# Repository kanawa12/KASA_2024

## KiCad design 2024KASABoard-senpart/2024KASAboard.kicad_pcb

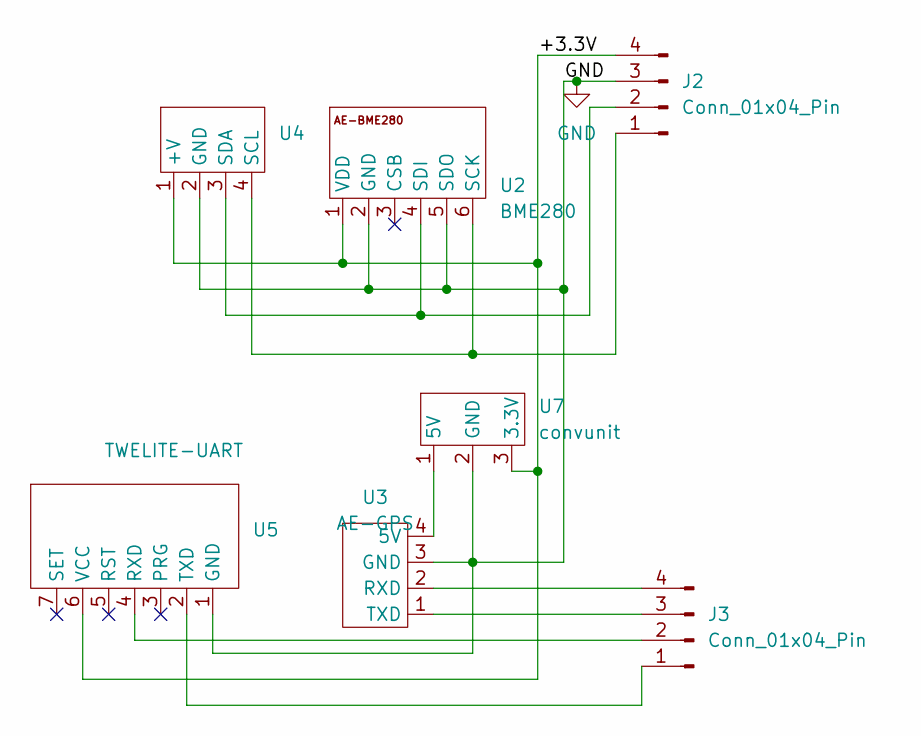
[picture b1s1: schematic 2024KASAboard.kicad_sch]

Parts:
J2, J3: Conn_01x04_Pin; JST_XH_S4B-XH-A_1x04_P2.50mm_Horizontal
U2: BME280; AE-BME280
U3: AE-GPS
U4: AE-LSM9DS1-I2C
U5: TWELITE-UART; MW-R-UART-U
U7: convunit; JST_VH_B3P-VH_1x03_P3.96mm_Vertical

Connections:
/+3.3V: J2.4, U2.1 (VDD), U4.1 (+V), U5.6 (VCC), U7.3 (3.3V)
GND: J2.3, U2.2 (GND), U2.5 (SDO), U3.3 (GND), U4.2 (GND), U5.1 (GND), U7.2 (GND)
unnamed: J2.1, U2.6 (SCK), U4.4 (SCL)
unnamed: J2.2, U2.4 (SDI), U4.3 (SDA)
unnamed: J3.1, U5.2 (TXD)
unnamed: J3.2, U5.4 (RXD)
unnamed: J3.3, U3.1 (TXD)
unnamed: J3.4, U3.2 (RXD)
unnamed: U3.4 (5V), U7.1 (5V)

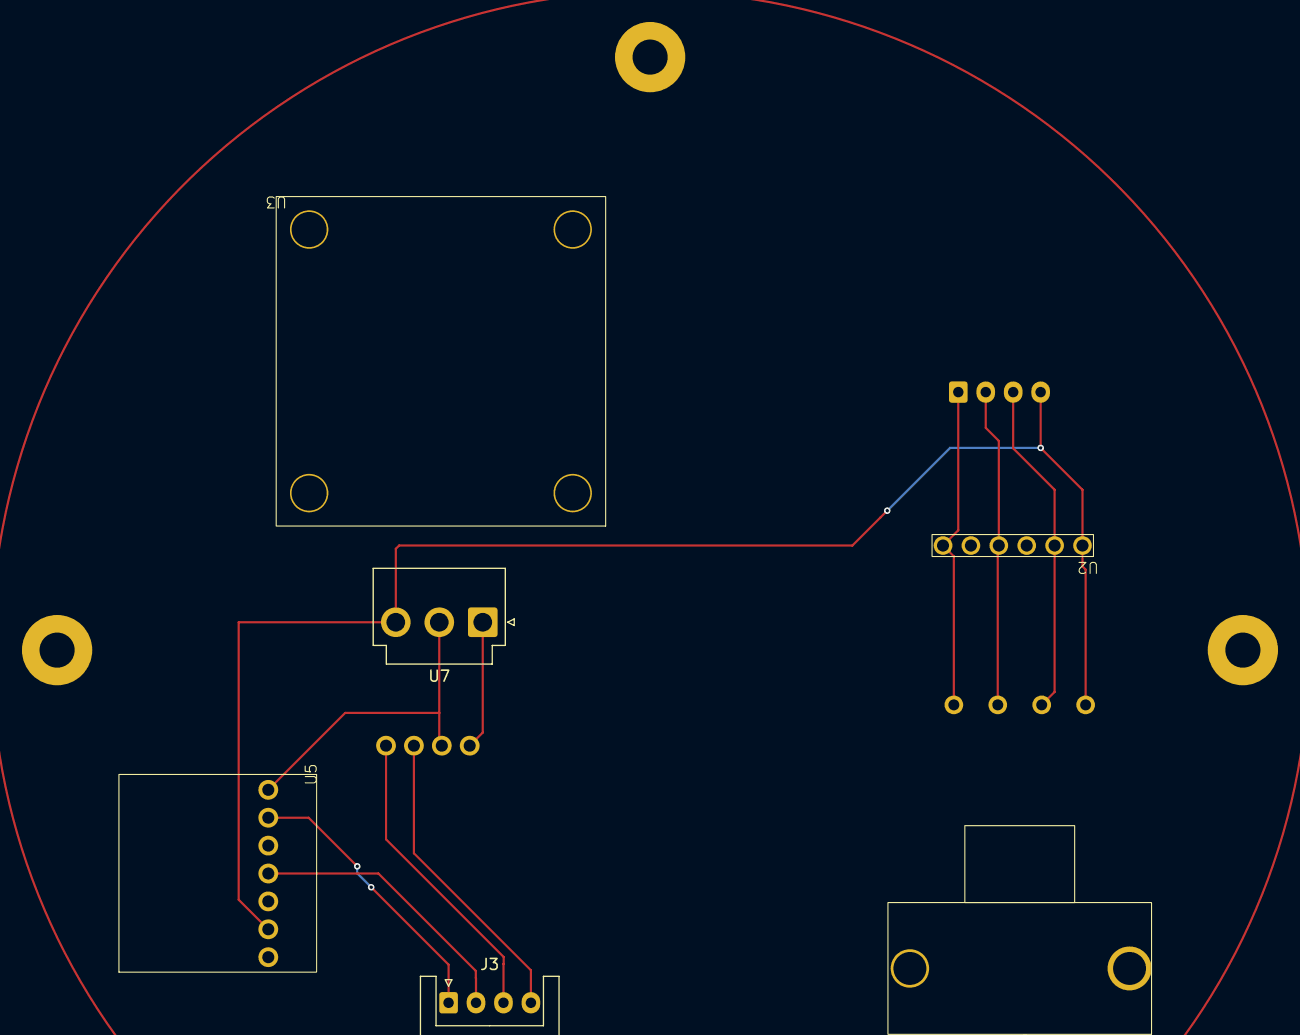
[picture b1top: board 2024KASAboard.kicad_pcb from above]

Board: 2 copper layers, 10 parts (1 on the bottom side), 9 nets.

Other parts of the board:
MH1, MH1#2, MH1#3: MountingHole_3.2mm_M3_Pad

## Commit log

2024-11-16 orange
2024-11-16 add-wire
2024-11-30 board_and_code
    ボードの修正とプログラムの追加
2024-11-30 add-sensor-sample
2024-11-30 set-mainfile
2024-12-13 fixTimer
2024-12-14 fixTimerAndSerial
2024-12-14 basesyscomp
    基本的な動作確認済み版
2024-12-14 basechk
    基本的な動作確認
2024-12-14 boardschcomp
    回路図(基本)
2024-12-14 base_sch_addbatt
2024-12-14 manual-fix
2024-12-14 addsdlib
2024-12-21 PCBdraft
